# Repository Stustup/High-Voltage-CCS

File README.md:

# High voltage constant current sorce/sink

I often need a simple low to medium current constant current source for tube amplifier projects. [Pete Millett recently released a CCS board](http://pmillett.com/CCS.html), but the integrated heatsink made it a bit too bulky for my taste and case of my DIY SET headphone amp (coming soon).

The CCS consists of a cascaded MosFET (or JFET for the lower device) topology as per for example "Valve Amplifiers by Morgan Jones p.152 (D)". 

You have the choice on every stage on what device you want to use. The upper stage sees most of the voltage drop, so you have the choice of a TO220 and a SOT89 package. Use the TO220 for possible power dissipations of above to 1W, the SOT89 for everything below. I did this to get the footprint even smaller when you need it, e.g. Anode Resistors in small current pre stages. 

In the lower stage you can choose between a SOT89 (same as above) and a SOT23 package. For currents above 5mA use the SOT89, for currents above use the SOT89 device. The SOT23 package can be a JFET to get low noise low current sinks/sources.

I added TVS diodes to protect the gates of the FETS. Measuring the current can be done via the V-Set pad. Just measure between this and the VSS pin. The current can be calculated via the measured voltage times the current-set resistor R3.

You can mark on the little cute table on the right side of the PCB which version you built to prevent confusion and possibly destroyed devices. 

As for setting the CCS beforehand, i connect it to either a bench top PSU with a voltage of around 20V or, if i dont have it, to a USB-C trigger board set to 20V. You can also turn the potentiometer to the lowerst possible current, but i fat fingered this too often and set the maximum current instead, destroying a way too expensive lateral MosFET in an audio amp.

Mister Millett added a Mu-out on his board for possible MU follower configurations. I never tried it, but included it anyways for experimentation purposes. Read on (his site how to use it)[http://pmillett.com/CCS.html].

The board gets its small size from the (if i may say so) relatively unconventional way you mount the board and it's TO220 package to the case. you only need a single mounting hole on your amp's case, an insulation washer and a (preferrably nylon) spacer. The mounting holes are made for M3 - M3.5 bolts.

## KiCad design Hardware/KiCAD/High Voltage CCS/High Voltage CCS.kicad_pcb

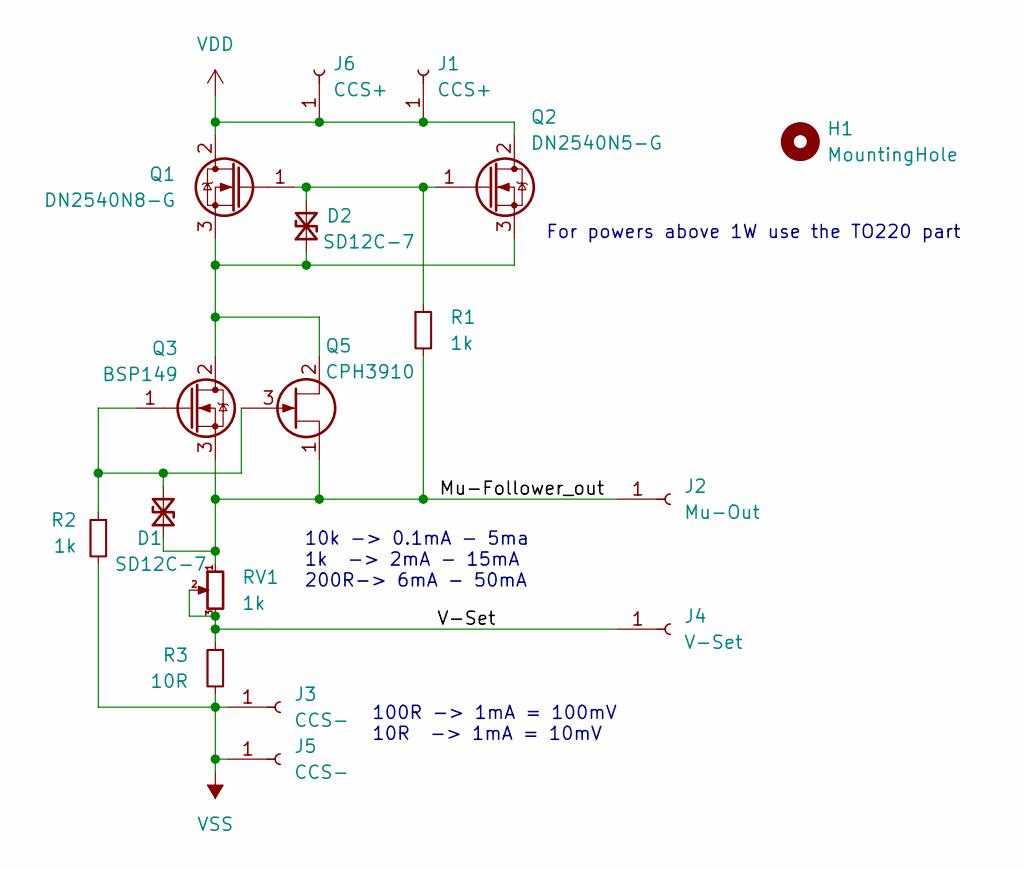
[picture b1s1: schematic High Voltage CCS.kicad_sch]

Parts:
D1, D2: SD12C-7; D_SOD-323_HandSoldering; Mouser Nr. 621-SD12C-7
H1: MountingHole; MountingHole_3.5mm
J1, J6: CCS+; Pin_D1.3mm_L11.0mm
J2: Mu-Out; Pin_D1.3mm_L11.0mm
J3, J5: CCS-; Pin_D1.3mm_L11.0mm
J4: V-Set; Pin_D1.3mm_L11.0mm
Q1: DN2540N8-G; SOT-89-3; Mouser-Nr. DN2540N8-G
Q2: DN2540N5-G; TO-220-3_Vertical; Mouser-Nr. 689-DN2540N5-G
Q3: BSP149; SOT-89-3; Mouser-Nr. DN2540N8-G
Q5: CPH3910; SOT-23_Handsoldering; Mouser Nr. 863-CPH3910-TL-E
R1, R2: 1k; R_0805_2012Metric_Pad1.20x1.40mm_HandSolder; Mouser-Nr. 603-RE0805FRE07330RL
R3: 10R; R_0805_2012Metric_Pad1.20x1.40mm_HandSolder; Mouser-Nr. 71-CRCW080510R0FKEAC
RV1: 1k; Potentiometer_Bourns_3296W_Vertical; Mouser-Nr. 81-PV36Y501C01B00

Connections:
/Mu-Follower_out: D1.1 (A1), J2.1, Q3.3 (S), Q5.1 (S), R1.2, RV1.1
/V-Set: J4.1, R3.1, RV1.2, RV1.3
unnamed: D1.2 (A2), Q3.1 (G), Q5.3 (G), R2.1
unnamed: D2.1 (A1), Q1.3 (S), Q2.3 (S), Q3.2 (D), Q5.2 (D)
unnamed: D2.2 (A2), Q1.1 (G), Q2.1 (G), R1.1
VDD: J1.1, J6.1, Q1.2 (D), Q2.2 (D)
VSS: J3.1, J5.1, R2.2, R3.2

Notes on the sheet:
10k -> 0.1mA - 5ma 1k -> 2mA - 15mA 200R-> 6mA - 50mA
For powers above 1W use the TO220 part
100R -> 1mA = 100mV 10R -> 1mA = 10mV

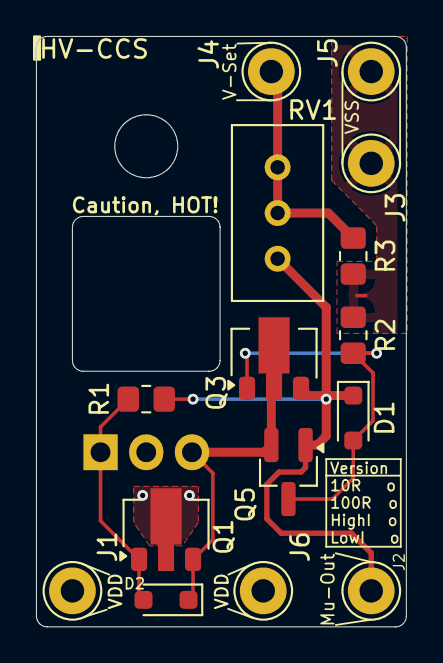
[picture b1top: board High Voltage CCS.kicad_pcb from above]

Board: 2 copper layers, 20.6 x 32.8 mm, 17 parts (1 on the bottom side), 7 nets.

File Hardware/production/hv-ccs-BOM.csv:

"Reference","Value","Mouser-Nr.","Footprint","Datasheet","Qty","DNP"
"D1,D2","SD12C-7","","Diode_SMD:D_SOD-323_HandSoldering","https://www.mouser.de/datasheet/2/115/DIOD_S_A0009691744_1-2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","2",""
"J1,J6","CCS+","","Connector_Pin:Pin_D1.3mm_L11.0mm","~","2",""
"J2","Mu-Out","","Connector_Pin:Pin_D1.3mm_L11.0mm","~","1",""
"J3,J5","CCS-","","Connector_Pin:Pin_D1.3mm_L11.0mm","~","2",""
"J4","V-Set","","Connector_Pin:Pin_D1.3mm_L11.0mm","~","1",""
"Q1","DN2540N8-G","DN2540N8-G ","Package_TO_SOT_SMD:SOT-89-3","https://ww1.microchip.com/downloads/en/DeviceDoc/DN2540%20B0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","1",""
"Q2","DN2540N5-G","689-DN2540N5-G","Package_TO_SOT_THT:TO-220-3_Vertical","https://ww1.microchip.com/downloads/en/DeviceDoc/DN2540%20B0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","1",""
"Q3","BSP149","DN2540N8-G ","Package_TO_SOT_SMD:SOT-89-3","https://www.mouser.de/datasheet/2/196/Infineon_BSP149_DS_v02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","1",""
"Q5","CPH3910","","Package_TO_SOT_SMD:SOT-23_Handsoldering","https://www.onsemi.com/PowerSolutions/product.do?id=CPH3910-TL-E","1",""
"R1,R2,RV1","1k","603-RE0805FRE07330RL,81-PV36Y501C01B00","Potentiometer_THT:Potentiometer_Bourns_3296W_Vertical,Resistor_SMD:R_0805_2012Metric_Pad1.20x1.40mm_HandSolder","~","3",""
"R3","10R","71-CRCW080510R0FKEAC","Resistor_SMD:R_0805_2012Metric_Pad1.20x1.40mm_HandSolder","~","1",""

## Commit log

2025-03-10 added everything :)
2025-03-10 added readme
2025-03-10 readme pflege
2025-03-10 added safety notice in redme
2025-03-10 mu out
2025-03-10 added side 3d yiew
2025-03-10 repair
2025-03-10 repaired readme
2025-03-10 rechtschreibfehler
2025-03-19 Create LICENSE
